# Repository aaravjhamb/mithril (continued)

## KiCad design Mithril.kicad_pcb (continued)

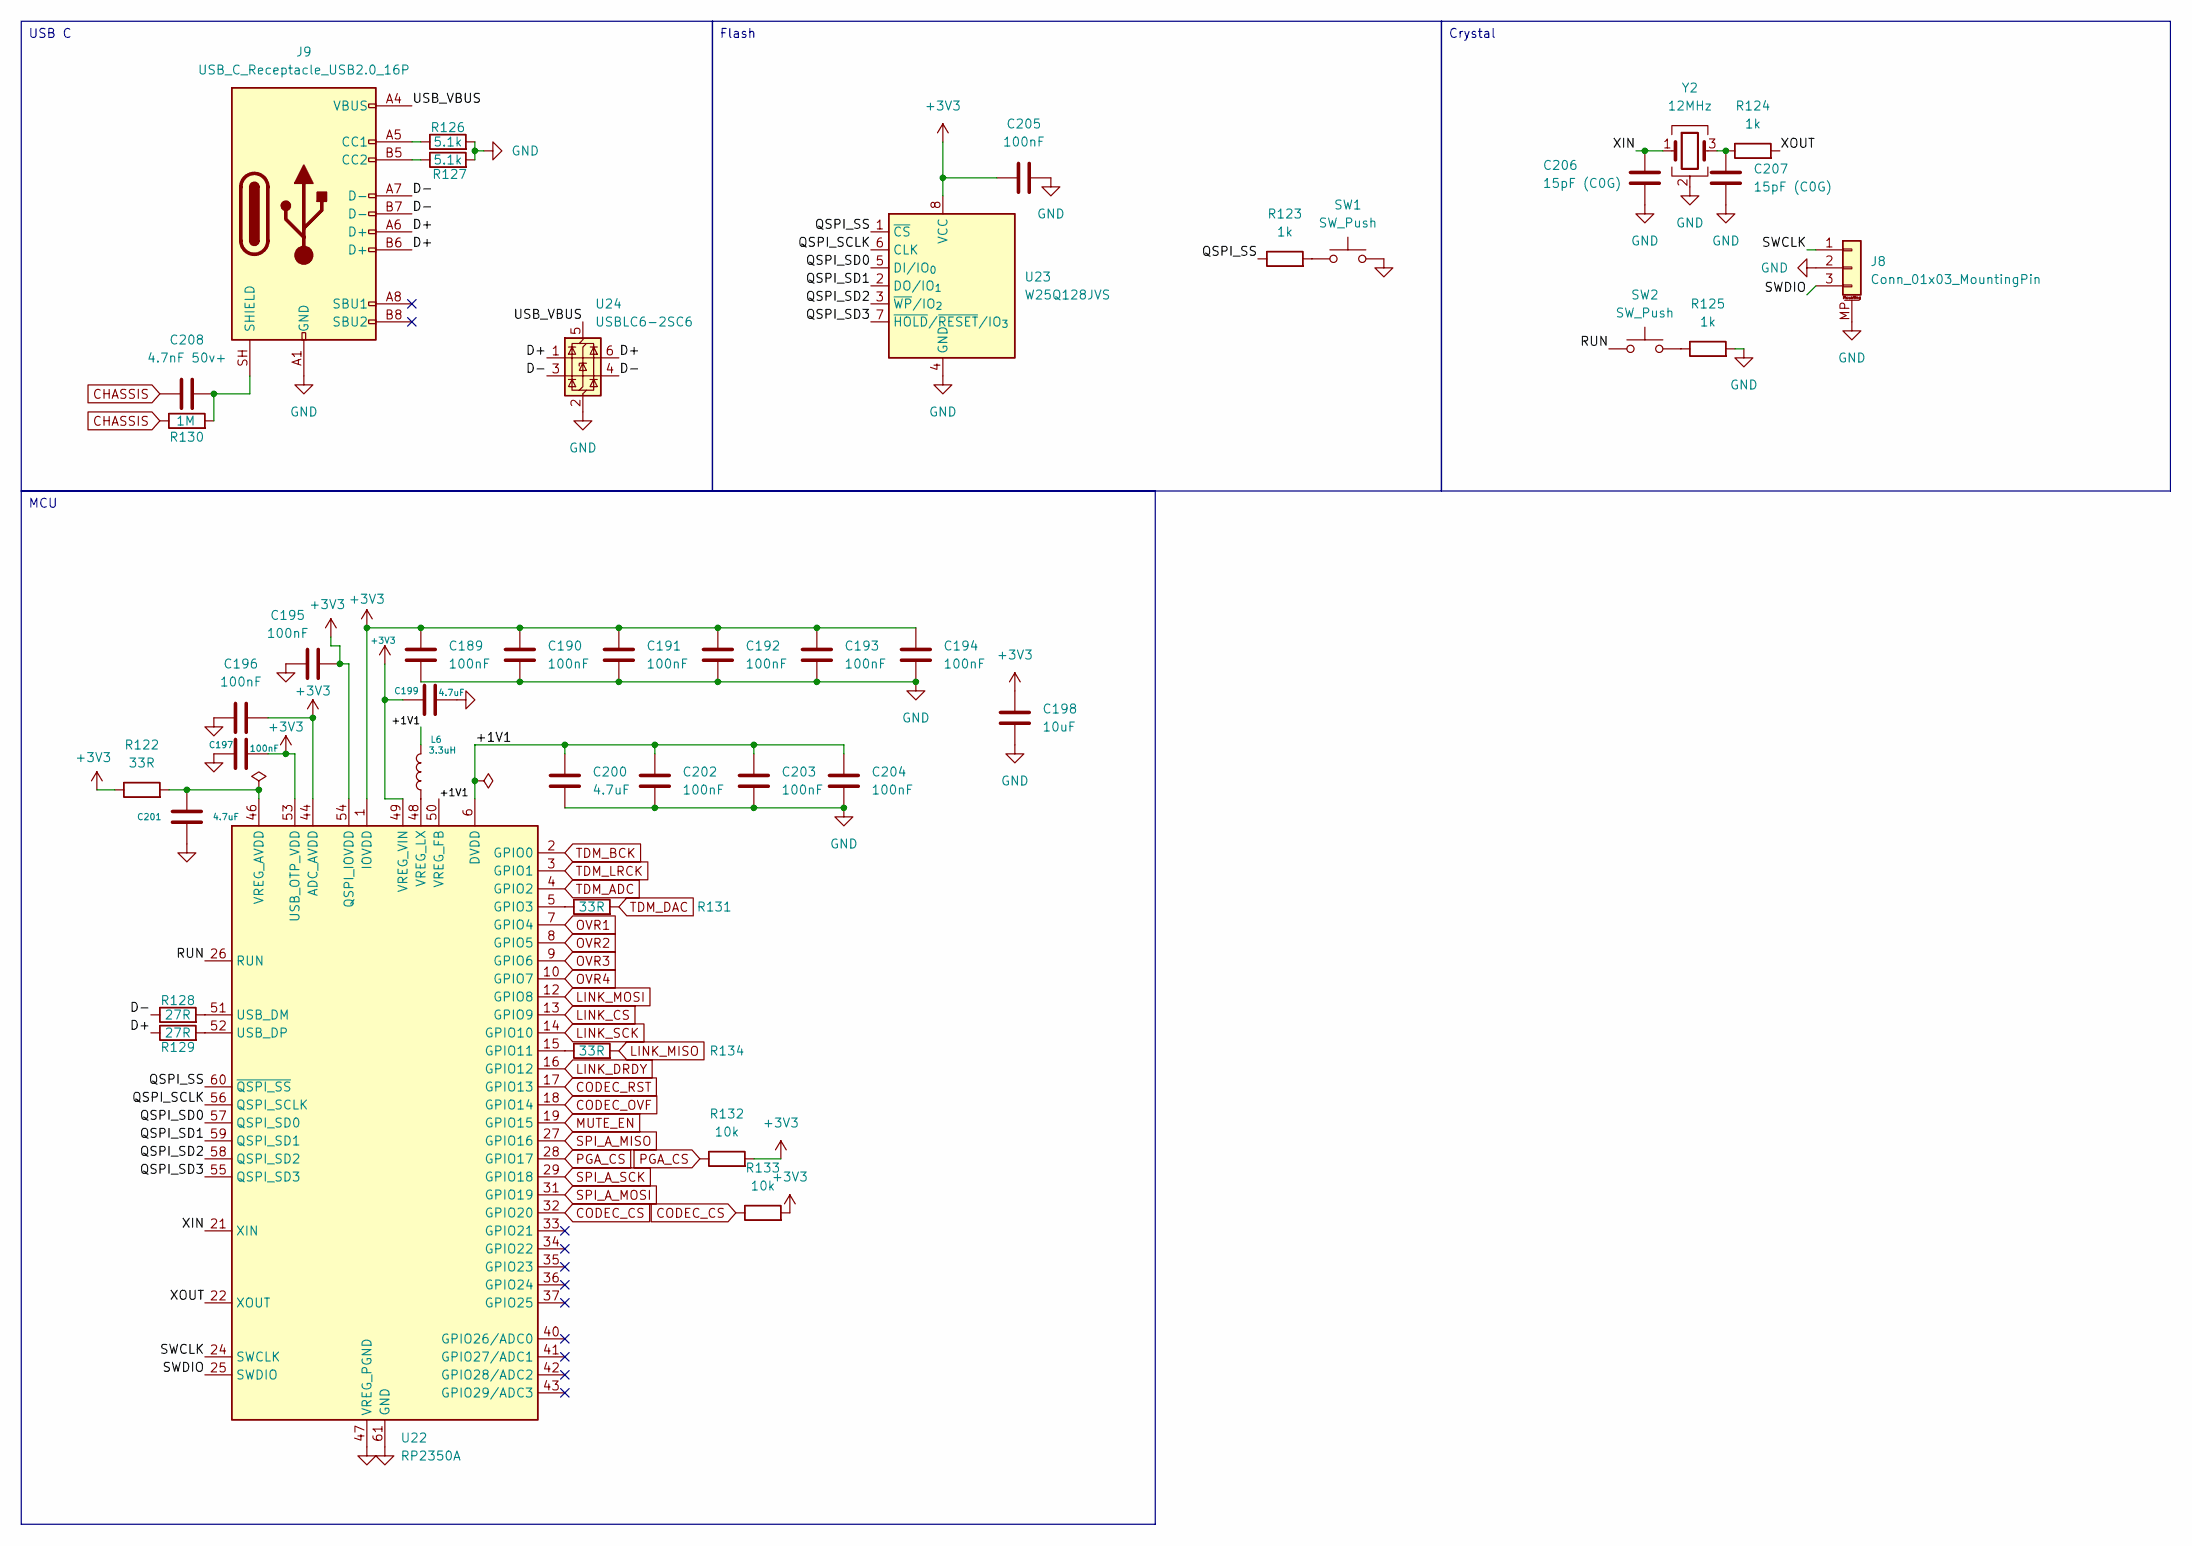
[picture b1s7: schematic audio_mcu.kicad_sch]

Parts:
C189, C190, C191, C192, C193, C194, C195, C196, C197, C202, C203, C204, C205: 100nF; C_0603_1608Metric
C198: 10uF; C_0805_2012Metric
C199, C200, C201: 4.7uF; C_0805_2012Metric
C206, C207: 15pF (C0G); C_0603_1608Metric
C208: 4.7nF 50v+; C_0603_1608Metric
J8: Conn_01x03_MountingPin; JST_SH_SM03B-SRSS-TB_1x03-1MP_P1.00mm_Horizontal
J9: USB_C_Receptacle_USB2.0_16P; USB_C_Receptacle_HRO_TYPE-C-31-M-12; LCSC Part C165948
L6: 3.3uH; L_Abracon_AOTA-B201610S
R122, R131, R134: 33R; R_0603_1608Metric
R123, R124, R125: 1k; R_0603_1608Metric
R126, R127: 5.1k; R_0603_1608Metric
R128, R129: 27R; R_0603_1608Metric
R130: 1M; R_0603_1608Metric
R132, R133: 10k; R_0603_1608Metric
SW1, SW2: SW_Push; SW_SPST_PTS810
U22: RP2350A; QFN-60-1EP_7x7mm_P0.4mm_EP3.4x3.4mm
U23: W25Q128JVS; SOIC-8_5.3x5.3mm_P1.27mm
U24: USBLC6-2SC6; SOT-23-6
Y2: 12MHz; Crystal_SMD_3225-4Pin_3.2x2.5mm

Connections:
+3V3: C189.1, C190.1, C191.1, C192.1, C193.1, C194.1, C195.2, C196.2, C197.2, C198.1, C199.1, C205.1, R122.1, R132.2, R133.2, U22.1 (IOVDD), U22.11 (IOVDD), U22.20 (IOVDD), U22.30 (IOVDD), U22.38 (IOVDD), U22.44 (ADC_AVDD), U22.45 (IOVDD), U22.49 (VREG_VIN), U22.53 (USB_OTP_VDD), U22.54 (QSPI_IOVDD), U23.8 (VCC); also elsewhere on the board
/audio_mcu/+1V1: C200.1, C202.1, C203.1, C204.1, L6.2, U22.6 (DVDD), U22.23 (DVDD), U22.39 (DVDD), U22.50 (VREG_FB)
/audio_mcu/D+: J9.A6 (D+), J9.B6 (D+), R129.1, U24.1 (I/O1), U24.6 (I/O1)
/audio_mcu/D-: J9.A7 (D-), J9.B7 (D-), R128.1, U24.3 (I/O2), U24.4 (I/O2)
/audio_mcu/QSPI_SCLK: U22.56 (QSPI_SCLK), U23.6 (CLK)
/audio_mcu/QSPI_SD0: U22.57 (QSPI_SD0), U23.5 (DI/IO_{0})
/audio_mcu/QSPI_SD1: U22.59 (QSPI_SD1), U23.2 (DO/IO_{1})
/audio_mcu/QSPI_SD2: U22.58 (QSPI_SD2), U23.3 (~WP/IO_{2})
/audio_mcu/QSPI_SD3: U22.55 (QSPI_SD3), U23.7 (~HOLD/~RESET/IO_{3})
/audio_mcu/QSPI_SS: R123.1, U22.60 (~QSPI_SS), U23.1 (~CS)
/audio_mcu/RUN: SW2.1, U22.26 (RUN)
/audio_mcu/SWCLK: J8.1, U22.24 (SWCLK)
/audio_mcu/SWDIO: J8.3, U22.25 (SWDIO)
/audio_mcu/USB_VBUS: J9.A4 (VBUS), J9.A9 (VBUS), J9.B4 (VBUS), J9.B9 (VBUS), U24.5 (VBUS)
/audio_mcu/XIN: C206.1, U22.21 (XIN), Y2.1
/audio_mcu/XOUT: R124.2, U22.22 (XOUT)
CHASSIS: C208.1, R130.1; also elsewhere on the board
CODEC_CS: R133.1, U22.32 (GPIO20); also elsewhere on the board
CODEC_OVF: U22.18 (GPIO14); also elsewhere on the board
CODEC_RST: U22.17 (GPIO13); also elsewhere on the board
GND: C189.2, C190.2, C191.2, C192.2, C193.2, C194.2, C195.1, C196.1, C197.1, C198.2, C199.2, C200.2, C201.2, C202.2, C203.2, C204.2, C205.2, C206.2, C207.2, J8.2, J8.MP (MountPin), J9.A1 (GND), J9.A12 (GND), J9.B1 (GND), J9.B12 (GND), R125.2, R126.2, R127.2, SW1.2, U22.47 (VREG_PGND), U22.61 (GND), U23.4 (GND), U24.2 (GND), Y2.2 (G), Y2.4 (G); also elsewhere on the board
LINK_CS: U22.13 (GPIO9); also elsewhere on the board
LINK_DRDY: U22.16 (GPIO12); also elsewhere on the board
LINK_MISO: R134.2; also elsewhere on the board
LINK_MOSI: U22.12 (GPIO8); also elsewhere on the board
LINK_SCK: U22.14 (GPIO10); also elsewhere on the board
MUTE_EN: U22.19 (GPIO15); also elsewhere on the board
unnamed: C207.1, R124.1, Y2.3
unnamed: J9.A5 (CC1), R126.1
unnamed: J9.B5 (CC2), R127.1
unnamed: C208.2, J9.SH (SHIELD), R130.2
unnamed: R123.2, SW1.1
unnamed: R125.1, SW2.2
unnamed: R131.1, U22.5 (GPIO3)
unnamed: R134.1, U22.15 (GPIO11)
unnamed: R128.2, U22.51 (USB_DM)
unnamed: R129.2, U22.52 (USB_DP)
unnamed: C201.1, R122.2, U22.46 (VREG_AVDD)
unnamed: L6.1, U22.48 (VREG_LX)
OVR1: U22.7 (GPIO4); also elsewhere on the board
OVR2: U22.8 (GPIO5); also elsewhere on the board
OVR3: U22.9 (GPIO6); also elsewhere on the board
OVR4: U22.10 (GPIO7); also elsewhere on the board
PGA_CS: R132.1, U22.28 (GPIO17); also elsewhere on the board
SPI_A_MISO: U22.27 (GPIO16); also elsewhere on the board
SPI_A_MOSI: U22.31 (GPIO19); also elsewhere on the board
SPI_A_SCK: U22.29 (GPIO18); also elsewhere on the board
TDM_ADC: U22.4 (GPIO2); also elsewhere on the board
TDM_BCK: U22.2 (GPIO0); also elsewhere on the board
TDM_DAC: R131.2; also elsewhere on the board
TDM_LRCK: U22.3 (GPIO1); also elsewhere on the board

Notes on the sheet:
MCU
USB C
Flash
Crystal

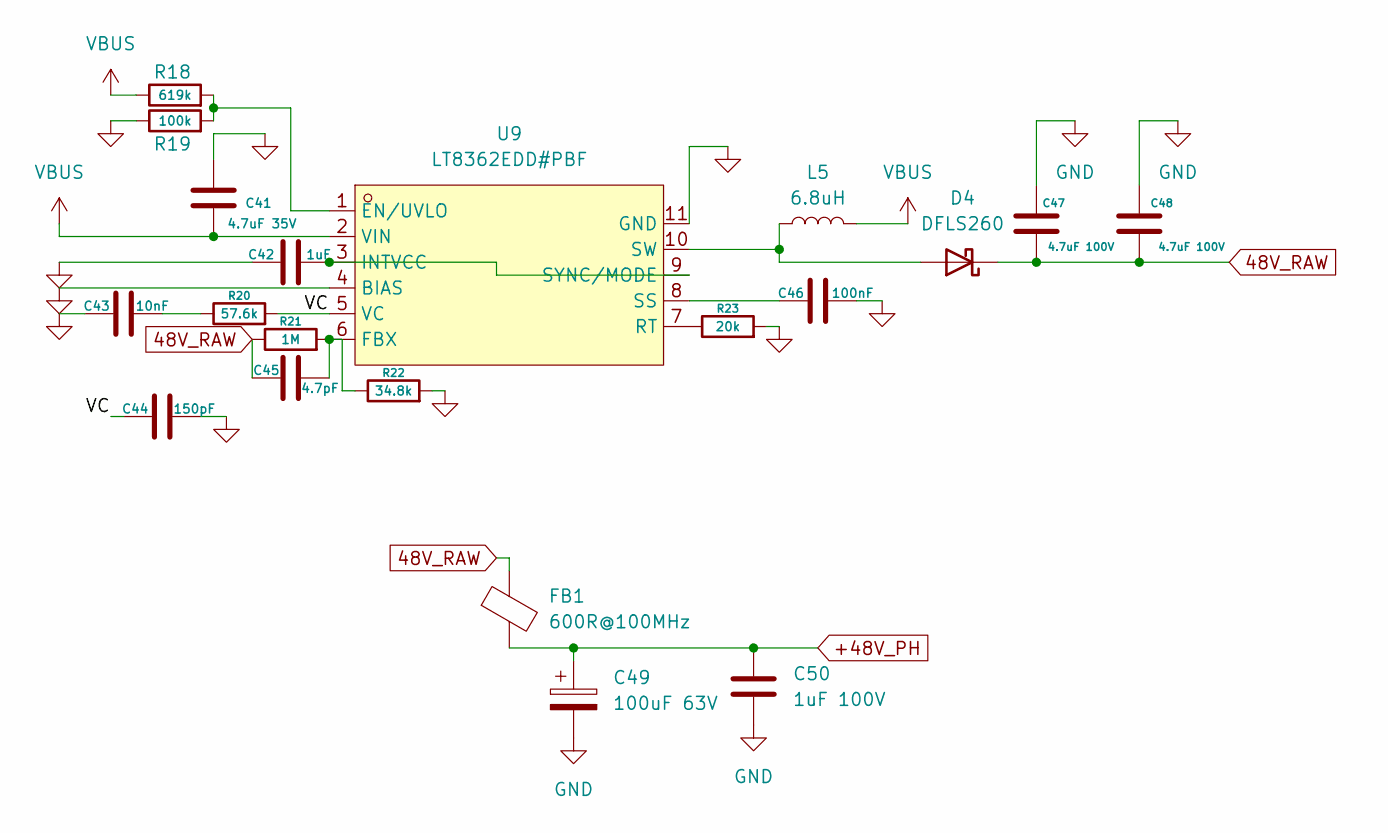
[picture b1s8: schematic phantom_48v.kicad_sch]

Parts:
C41: 4.7uF 35V; C_1206_3216Metric
C42: 1uF; C_0603_1608Metric
C43: 10nF; C_0603_1608Metric
C44: 150pF; C_0603_1608Metric
C45: 4.7pF; C_0603_1608Metric
C46: 100nF; C_0603_1608Metric
C47, C48: 4.7uF 100V; C_1210_3225Metric
C49: 100uF 63V; CP_Elec_10x10.5
C50: 1uF 100V; C_1206_3216Metric
D4: DFLS260; D_PowerDI-123
FB1: 600R@100MHz; L_0603_1608Metric
L5: 6.8uH; L_Sunlord_MWSA0518S; LCSC Part C408348
R18: 619k; R_0603_1608Metric
R19: 100k; R_0603_1608Metric
R20: 57.6k; R_0603_1608Metric
R21: 1M; R_0805_2012Metric
R22: 34.8k; R_0603_1608Metric
R23: 20k; R_0603_1608Metric
U9: LT8362EDD#PBF; DFN-10_L3.0-W3.0-P0.50-TL-EP2.4; MPN LT8362EDD#PBF; LCSC Part C673761

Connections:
48V_RAW: C45.1, C47.2, C48.2, D4.1 (K), FB1.1, R21.1
+48V_PH: C49.1, C50.1, FB1.2; also elsewhere on the board
/phantom_48v/VC: C44.1, R20.2, U9.5 (VC)
GND: C41.1, C42.1, C43.1, C44.2, C46.2, C47.1, C48.1, C49.2, C50.2, R19.1, R22.2, R23.2, U9.4 (BIAS), U9.11 (GND); also elsewhere on the board
unnamed: C43.2, R20.1
unnamed: D4.2 (A), L5.1, U9.10 (SW)
unnamed: R18.2, R19.2, U9.1 (EN/UVLO)
unnamed: C45.2, R21.2, R22.1, U9.6 (FBX)
unnamed: C42.2, U9.3 (INTVCC), U9.9 (SYNC/MODE)
unnamed: R23.1, U9.7 (RT)
unnamed: C46.1, U9.8 (SS)
VBUS: C41.2, L5.2, R18.1, U9.2 (VIN); also elsewhere on the board

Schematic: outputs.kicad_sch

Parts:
C286: 10u; C_0805_2012Metric
C287, C288: 100n; C_0603_1608Metric
C289, C290: 1u; C_0603_1608Metric
J14, J15, J16, J17, J18, J19: NC3MAH; Jack_XLR_Neutrik_NC3MAH_Horizontal; LCSC Part C5154126
J20: NRJ6HF; Jack_6.35mm_Neutrik_NRJ6HF_Horizontal
Q5: AO3400A; SOT-23
R202: 100R; R_0603_1608Metric
R203: 100K; R_0603_1608Metric
U34: TPA6132A2RTE; WQFN-16-1EP_3x3mm_P0.5mm_EP1.6x1.6mm_ThermalVias

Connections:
+5V_A: C286.2, C287.1, C288.1, U34.12 (HPVDD), U34.14 (VDD); also elsewhere on the board
AUX1_COLD: J16.3; also elsewhere on the board
AUX1_HOT: J16.2; also elsewhere on the board
AUX2_COLD: J17.3; also elsewhere on the board
AUX2_HOT: J17.2; also elsewhere on the board
AUX3_COLD: J18.3; also elsewhere on the board
AUX3_HOT: J18.2; also elsewhere on the board
AUX4_COLD: J19.3; also elsewhere on the board
AUX4_HOT: J19.2; also elsewhere on the board
CHASSIS: J14.1, J14.G, J15.1, J15.G, J16.1, J16.G, J17.1, J17.G, J18.1, J18.G, J19.1, J19.G; also elsewhere on the board
GND: C286.1, C287.2, C288.2, C289.1, J20.S, Q5.2 (S), R203.1, U34.1 (INL-), U34.4 (INR-), U34.6 (G0), U34.7 (G1), U34.10 (PGND), U34.15 (SGND), U34.17 (EP); also elsewhere on the board
HP_L: J20.T, U34.16 (OUTL)
HP_R: J20.R, U34.5 (OUTR)
MAIN_L_COLD: J14.3; also elsewhere on the board
MAIN_L_HOT: J14.2; also elsewhere on the board
MAIN_R_COLD: J15.3; also elsewhere on the board
MAIN_R_HOT: J15.2; also elsewhere on the board
MUTE_EN: R202.2, U34.13 (EN); also elsewhere on the board
unnamed: Q5.1 (G), R202.1, R203.2
unnamed: C290.2, U34.9 (CPN)
unnamed: C290.1, U34.11 (CPP)
unnamed: C289.2, U34.8 (HPVSS)
PHONES_L: U34.2 (INL+); also elsewhere on the board
PHONES_R: U34.3 (INR+); also elsewhere on the board
RELAY_DRV: Q5.3 (D); also elsewhere on the board

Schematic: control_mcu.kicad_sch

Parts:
C209, C211, C212, C213, C214, C216, C218, C219, C220, C221, C222, C223, C224, C226: 100nF; C_0603_1608Metric
C210, C215, C217: 4.7uF; C_0805_2012Metric
C225, C229: 10uF; C_0805_2012Metric
C227, C228: 15pF (C0G); C_0603_1608Metric
D21: LED; LED_0603_1608Metric
F2: Polyfuse 500mA; Fuse_1206_3216Metric
J10, J12: Conn_01x06; PinSocket_1x06_P2.54mm_Vertical
J11: Conn_01x03_MountingPin; JST_SH_SM03B-SRSS-TB_1x03-1MP_P1.00mm_Horizontal
J13: Conn_02x03_Odd_Even; IDC-Header_2x03_P2.54mm_Vertical
L7: 3.3uH; L_Abracon_AOTA-B201610S
R135, R136, R137, R138: 33R; R_0603_1608Metric
R139: 330R; R_0603_1608Metric
R140, R141: 10k; R_0603_1608Metric
R142: 100R; R_0603_1608Metric
R145, R146, R147: 1k; R_0603_1608Metric
SW3, SW4: SW_Push; SW_SPST_PTS810
U25: RP2350A; QFN-60-1EP_7x7mm_P0.4mm_EP3.4x3.4mm
U27: W25Q128JVS; SOIC-8_5.3x5.3mm_P1.27mm
Y3: 12MHz; Crystal_SMD_3225-4Pin_3.2x2.5mm

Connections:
+3V3: C209.1, C211.2, C212.2, C213.2, C214.1, C215.1, C216.1, C218.1, C220.1, C222.1, C224.1, C225.1, C226.1, C229.1, F2.1, J12.2, J12.3, R135.1, R140.2, R141.2, U25.1 (IOVDD), U25.11 (IOVDD), U25.20 (IOVDD), U25.30 (IOVDD), U25.38 (IOVDD), U25.44 (ADC_AVDD), U25.45 (IOVDD), U25.49 (VREG_VIN), U25.53 (USB_OTP_VDD), U25.54 (QSPI_IOVDD), U27.8 (VCC); also elsewhere on the board
/control_mcu/+1V1: C217.1, C219.1, C221.1, C223.1, L7.2, U25.6 (DVDD), U25.23 (DVDD), U25.39 (DVDD), U25.50 (VREG_FB)
/control_mcu/QSPI_SCLK: U25.56 (QSPI_SCLK), U27.6 (CLK)
/control_mcu/QSPI_SD0: U25.57 (QSPI_SD0), U27.5 (DI/IO_{0})
/control_mcu/QSPI_SD1: U25.59 (QSPI_SD1), U27.2 (DO/IO_{1})
/control_mcu/QSPI_SD2: U25.58 (QSPI_SD2), U27.3 (~WP/IO_{2})
/control_mcu/QSPI_SD3: U25.55 (QSPI_SD3), U27.7 (~HOLD/~RESET/IO_{3})
/control_mcu/QSPI_SS: R145.1, U25.60 (~QSPI_SS), U27.1 (~CS)
/control_mcu/RUN: SW4.1, U25.26 (RUN)
/control_mcu/SWCLK: J11.1, U25.24 (SWCLK)
/control_mcu/SWDIO: J11.3, U25.25 (SWDIO)
/control_mcu/XIN: C227.1, U25.21 (XIN), Y3.1
/control_mcu/XOUT: R147.2, U25.22 (XOUT)
ETH_CS: J10.5, U25.28 (GPIO17)
ETH_INT: J10.6, R140.1, U25.32 (GPIO20)
ETH_MISO: J12.6, U25.27 (GPIO16)
ETH_MOSI: J10.3, U25.31 (GPIO19)
ETH_RST: J12.5, R141.1, U25.33 (GPIO21)
ETH_SCK: J10.4, U25.29 (GPIO18)
GND: C209.2, C210.2, C211.1, C212.1, C213.1, C214.2, C215.2, C216.2, C217.2, C218.2, C219.2, C220.2, C221.2, C222.2, C223.2, C224.2, C225.2, C226.2, C227.2, C228.2, C229.2, D21.1 (K), J10.1, J10.2, J11.2, J11.MP (MountPin), J12.1, J13.2, J13.4, J13.6, R146.2, SW3.2, U25.47 (VREG_PGND), U25.61 (GND), U27.4 (GND), Y3.2 (G), Y3.4 (G); also elsewhere on the board
LINK_CS: R136.2; also elsewhere on the board
LINK_DRDY: U25.16 (GPIO12); also elsewhere on the board
LINK_MISO: U25.12 (GPIO8); also elsewhere on the board
LINK_MOSI: R138.2; also elsewhere on the board
LINK_SCK: R137.2; also elsewhere on the board
unnamed: C228.1, R147.1, Y3.3
unnamed: D21.2 (A), R139.2
unnamed: F2.2, J13.1
unnamed: J13.3, R142.2
unnamed: R145.2, SW3.1
unnamed: R146.1, SW4.2
unnamed: R136.1, U25.13 (GPIO9)
unnamed: R137.1, U25.14 (GPIO10)
unnamed: R138.1, U25.15 (GPIO11)
unnamed: R139.1, U25.37 (GPIO25)
unnamed: C210.1, R135.2, U25.46 (VREG_AVDD)
unnamed: L7.1, U25.48 (VREG_LX)
UART_C2P: R142.1, U25.7 (GPIO4)
UART_P2C: J13.5, U25.8 (GPIO5)
VBUS_SENSE: U25.40 (GPIO26/ADC0); also elsewhere on the board

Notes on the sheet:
Ethernet
Crystal
Flash
MCU

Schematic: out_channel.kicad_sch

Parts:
C230, C231: 10uF 25V bipolar; CP_Elec_6.3x5.4
C232, C233: 680pF COG; C_0603_1608Metric
C234, C235: 150pF COG; C_0603_1608Metric
C236, C237: 100nF; C_0603_1608Metric
D22: 1N4148W; D_SOD-123
K1: G6K-2F-Y-DC5; RELAY-SMD_G6K-2F-X-XX; MPN G6K-2F-Y-TR DC5; LCSC Part C47190
R143, R144, R148, R149, R150, R151: 10k 1%; R_0603_1608Metric
R152, R153: 47R; R_0603_1608Metric
U26: OPA1678; SOIC-8_3.9x4.9mm_P1.27mm

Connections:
+5V: D22.1 (K), K1.1; also elsewhere on the board
+5V_A: C236.1, U26.8 (V+); also elsewhere on the board
/outputs/out1/COLD_F: K1.5, R153.2
/outputs/out1/HOT_F: K1.4, R152.2
/outputs/out1/XA: C232.1, R143.2, R148.2, R150.1
/outputs/out1/XB: C233.1, R144.2, R149.2, R151.1
DAC1_N: C230.1; also elsewhere on the board
DAC1_P: C231.1; also elsewhere on the board
GND: C232.2, C233.2, C236.2, C237.2, K1.2, K1.7, U26.3 (+), U26.5 (+); also elsewhere on the board
MAIN_L_COLD: K1.6; also elsewhere on the board
MAIN_L_HOT: K1.3; also elsewhere on the board
unnamed: C230.2, R143.1
unnamed: C231.2, R144.1
unnamed: C234.2, R148.1, R152.1, U26.1
unnamed: C235.2, R149.1, R153.1, U26.7
unnamed: C234.1, R150.2, U26.2 (-)
unnamed: C235.1, R151.2, U26.6 (-)
RELAY_DRV: D22.2 (A), K1.8; also elsewhere on the board
−5V_A: C237.1, U26.4 (V-); also elsewhere on the board

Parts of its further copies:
C238, C241, C246, C249, C254, C257, C262, C265, C270, C273, C278, C281: 100nF; C_0603_1608Metric
C239, C240, C247, C248, C255, C256, C263, C264, C271, C272, C279, C280: 150pF COG; C_0603_1608Metric
C242, C245, C250, C253, C258, C261, C266, C269, C274, C277, C282, C285: 680pF COG; C_0603_1608Metric
C243, C244, C251, C252, C259, C260, C267, C268, C275, C276, C283, C284: 10uF 25V bipolar; CP_Elec_6.3x5.4
D23, D24, D25, D26, D27, D28: 1N4148W; D_SOD-123
K2, K3, K4, K5, K6, K7: G6K-2F-Y-DC5; RELAY-SMD_G6K-2F-X-XX; MPN G6K-2F-Y-TR DC5; LCSC Part C47190
R154, R155, R156, R158, R160, R161, R162, R163, R164, R166, R168, R169, R170, R171, R172, R174, R176, R177, R178, R179, R180, R182, R184, R185, R186, R187, R188, R190, R192, R193, R194, R195, R196, R198, R200, R201: 10k 1%; R_0603_1608Metric
R157, R159, R165, R167, R173, R175, R181, R183, R189, R191, R197, R199: 47R; R_0603_1608Metric
U28, U29, U30, U31, U32, U33: OPA1678; SOIC-8_3.9x4.9mm_P1.27mm

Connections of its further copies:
+5V: D23.1 (K), D24.1 (K), D25.1 (K), D26.1 (K), D27.1 (K), D28.1 (K), K2.1, K3.1, K4.1, K5.1, K6.1, K7.1; also elsewhere on the board
+5V_A: C238.1, C246.1, C254.1, C262.1, C270.1, C278.1, U28.8 (V+), U29.8 (V+), U30.8 (V+), U31.8 (V+), U32.8 (V+), U33.8 (V+); also elsewhere on the board
/outputs/out2/COLD_F: K2.5, R157.2
/outputs/out2/HOT_F: K2.4, R159.2
/outputs/out2/XA: C242.1, R154.1, R158.2, R160.2
/outputs/out2/XB: C245.1, R155.1, R156.2, R161.2
/outputs/out3/COLD_F: K3.5, R165.2
/outputs/out3/HOT_F: K3.4, R167.2
/outputs/out3/XA: C250.1, R162.1, R166.2, R168.2
/outputs/out3/XB: C253.1, R163.1, R164.2, R169.2
/outputs/out4/COLD_F: K4.5, R173.2
/outputs/out4/HOT_F: K4.4, R175.2
/outputs/out4/XA: C258.1, R170.1, R174.2, R176.2
/outputs/out4/XB: C261.1, R171.1, R172.2, R177.2
/outputs/out5/COLD_F: K5.5, R181.2
/outputs/out5/HOT_F: K5.4, R183.2
/outputs/out5/XA: C266.1, R178.1, R182.2, R184.2
/outputs/out5/XB: C269.1, R179.1, R180.2, R185.2
/outputs/out6/COLD_F: K6.5, R189.2
/outputs/out6/HOT_F: K6.4, R191.2
/outputs/out6/XA: C274.1, R186.1, R190.2, R192.2
/outputs/out6/XB: C277.1, R187.1, R188.2, R193.2
/outputs/out7/COLD_F: K7.5, R197.2
/outputs/out7/HOT_F: K7.4, R199.2
/outputs/out7/XA: C282.1, R194.1, R198.2, R200.2
/outputs/out7/XB: C285.1, R195.1, R196.2, R201.2
AUX1_COLD: K3.6; also elsewhere on the board
AUX1_HOT: K3.3; also elsewhere on the board
AUX2_COLD: K4.6; also elsewhere on the board
AUX2_HOT: K4.3; also elsewhere on the board
AUX3_COLD: K5.6; also elsewhere on the board
AUX3_HOT: K5.3; also elsewhere on the board
AUX4_COLD: K6.6; also elsewhere on the board
AUX4_HOT: K6.3; also elsewhere on the board
DAC2_N: C243.1; also elsewhere on the board
DAC2_P: C244.1; also elsewhere on the board
DAC3_N: C251.1; also elsewhere on the board
DAC3_P: C252.1; also elsewhere on the board
DAC4_N: C259.1; also elsewhere on the board
DAC4_P: C260.1; also elsewhere on the board
DAC5_N: C267.1; also elsewhere on the board
DAC5_P: C268.1; also elsewhere on the board
DAC6_N: C275.1; also elsewhere on the board
DAC6_P: C276.1; also elsewhere on the board
DAC7_N: C283.1; also elsewhere on the board
DAC8_N: C284.1; also elsewhere on the board
GND: C238.2, C241.2, C242.2, C245.2, C246.2, C249.2, C250.2, C253.2, C254.2, C257.2, C258.2, C261.2, C262.2, C265.2, C266.2, C269.2, C270.2, C273.2, C274.2, C277.2, C278.2, C281.2, C282.2, C285.2, K2.2, K2.7, K3.2, K3.7, K4.2, K4.7, K5.2, K5.7, K6.2, K6.7, K7.2, K7.7, U28.3 (+), U28.5 (+), U29.3 (+), U29.5 (+), U30.3 (+), U30.5 (+), U31.3 (+), U31.5 (+), U32.3 (+), U32.5 (+), U33.3 (+), U33.5 (+); also elsewhere on the board
MAIN_R_COLD: K2.6; also elsewhere on the board
MAIN_R_HOT: K2.3; also elsewhere on the board
unnamed: C239.2, R156.1, R157.1, U28.7
unnamed: C240.2, R158.1, R159.1, U28.1
unnamed: C243.2, R160.1
unnamed: C244.2, R161.1
unnamed: C247.2, R164.1, R165.1, U29.7
unnamed: C248.2, R166.1, R167.1, U29.1
unnamed: C251.2, R168.1
unnamed: C252.2, R169.1
unnamed: C255.2, R172.1, R173.1, U30.7
unnamed: C256.2, R174.1, R175.1, U30.1
unnamed: C259.2, R176.1
unnamed: C260.2, R177.1
unnamed: C263.2, R180.1, R181.1, U31.7
unnamed: C264.2, R182.1, R183.1, U31.1
unnamed: C267.2, R184.1
unnamed: C268.2, R185.1
unnamed: C271.2, R188.1, R189.1, U32.7
unnamed: C272.2, R190.1, R191.1, U32.1
unnamed: C275.2, R192.1
unnamed: C276.2, R193.1
unnamed: C279.2, R196.1, R197.1, U33.7
unnamed: C280.2, R198.1, R199.1, U33.1
unnamed: C283.2, R200.1
unnamed: C284.2, R201.1
unnamed: C240.1, R154.2, U28.2 (-)
unnamed: C239.1, R155.2, U28.6 (-)
unnamed: C248.1, R162.2, U29.2 (-)
unnamed: C247.1, R163.2, U29.6 (-)
unnamed: C256.1, R170.2, U30.2 (-)
unnamed: C255.1, R171.2, U30.6 (-)
unnamed: C264.1, R178.2, U31.2 (-)
unnamed: C263.1, R179.2, U31.6 (-)
unnamed: C272.1, R186.2, U32.2 (-)
unnamed: C271.1, R187.2, U32.6 (-)
unnamed: C280.1, R194.2, U33.2 (-)
unnamed: C279.1, R195.2, U33.6 (-)
PHONES_L: K7.3; also elsewhere on the board
PHONES_R: K7.6; also elsewhere on the board
RELAY_DRV: D23.2 (A), D24.2 (A), D25.2 (A), D26.2 (A), D27.2 (A), D28.2 (A), K2.8, K3.8, K4.8, K5.8, K6.8, K7.8; also elsewhere on the board
−5V_A: C241.1, C249.1, C257.1, C265.1, C273.1, C281.1, U28.4 (V-), U29.4 (V-), U30.4 (V-), U31.4 (V-), U32.4 (V-), U33.4 (V-); also elsewhere on the board

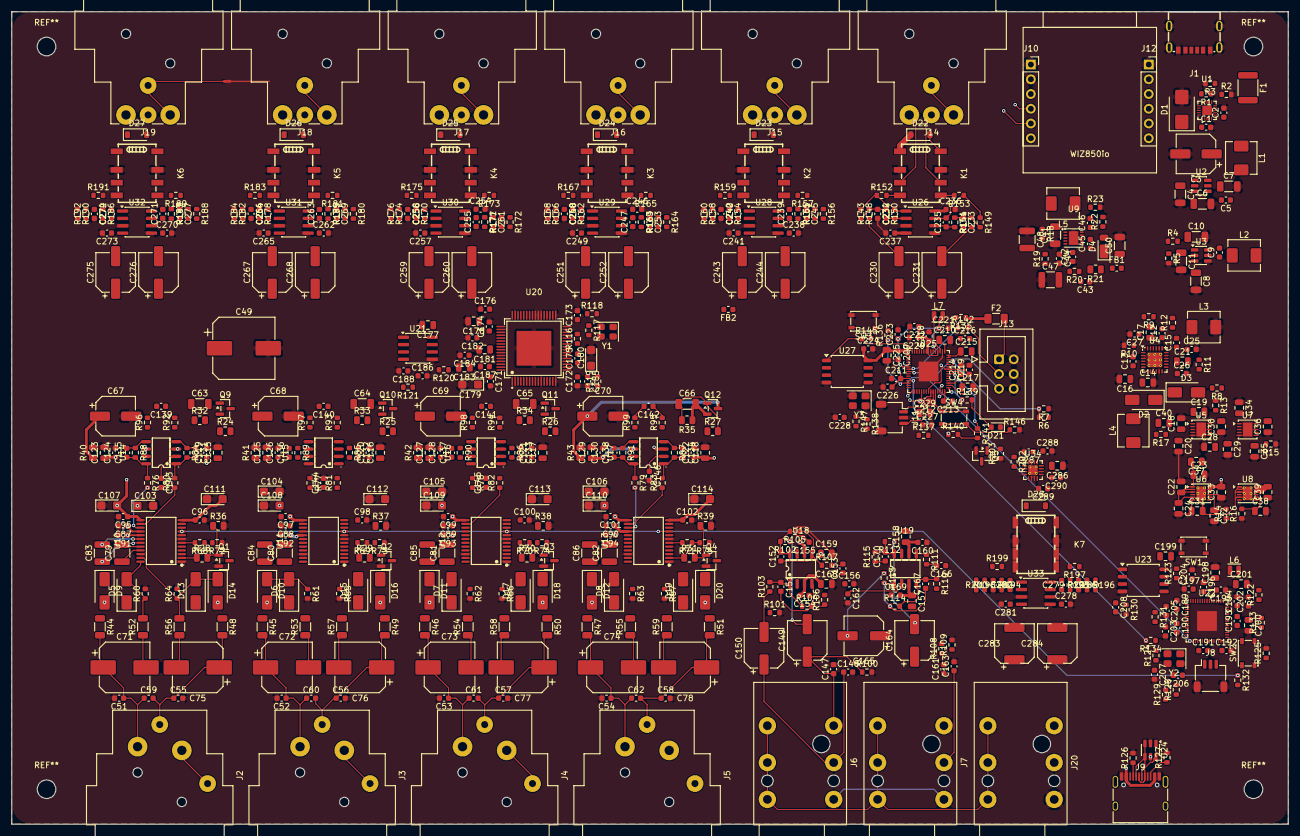
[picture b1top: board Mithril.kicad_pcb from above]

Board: 6 copper layers, 220.0 x 140.0 mm, 610 parts (0 on the bottom side), 364 nets.
